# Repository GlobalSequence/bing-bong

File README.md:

## Intro

Bing Bong is a digital drum synthesizer module for Eurorack synthesizers which generates percussive sounds using two different synthesis methods:

- Phase modulation synthesis
- Physical modeling synthesis

This module is intended to offer a versatile array of sounds ranging anywhere from organic substrates to purely synthesized tones. With a wide frequency range, it can fill many roles in an electronic drum kit. Both atonal and tonal sounds can be produced, ranging anywhere from quick transient bursts to long sustained sounds. 

## Block Diagram

## Features
- Versatile drum voice for modular synthesizers
- Switchable phase modulation and physical modeling sound engines
- Mechanical key switch for tactile manual triggering
- CV inputs for all parameters
- 12 bit, 48khz sound

## Synthesis Engines 
### Phase Modulation
#### Overview
The Phase modulation engine is made up of three sine wave operators, fed into one another in series, The first modulator has operator feedback.

The modulation index of each modulator is controlled by the envelope, with each index being set to maximum when the module is triggered, before fading to an index of 0 when the envelope has faded away, effectively creating a sharp sound which softens over time. 

This engine can be used to achieve deep raunchy kick drums, clean ringing chimes, metallic clangs, chirps, and more.
#### Parameters
##### Carrier 
This may be somewhat misleading as this parameter controls the base pitch of the entire voice. 
##### Modulator
Move the pitch of the two modulator oscillators relative to the pitch of the carrier oscillator. The first modulator is always an octave higher than the second modulator. 

When set very high, the carrier frequency (if also set very high) may push the modulator frequencies into interesting territories, or even to oblivion. There is no anti-aliasing in this module, and that's a feature, not a bug! 
##### Pitch Mod
Set the depth by which the envelope affects the pitch of all oscillators. With this parameter set to zero, there is no pitch modulation. As the pitch mod is turned up, the drum hit will start at increasingly higher frequencies and fall to the lowest frequency at the end of the envelope's decay.
##### Decay
Sets the decay time of the envelope. The envelope modulates these other parameters in the engine:
- Modulation index
- Pitch modulation amount
- Internal VCA
By shortening or lengthening the decay time, you can dramatically alter the trajectory of the sound, because all of the parameters dependent on it.

The decay time can be set from a few milliseconds to several seconds, turning the drum module into a sort of faux-drone that can be used for effects and sound scapes, should you wish to venture into that territory.

### Physical Modeling
#### Overview
The physical modeling engine is comprised of a white noise source which is fed into seven parallel band pass filters with a variable Q. 

This engine can be used to achieve organic drum tones ranging from membrane drums of many shapes and sizes, to percussive surfaces made of other materials like glass, metal, wood, and more. 
#### Parameters
##### Cutoff
This sets the cutoff frequency of the central and peripheral band pass filters. 
##### Spread
Pushes the 6 peripheral band pass filters away from the central filter. 3 peripheral filters are set to a lower frequency than the central filter, while the other 3 are higher. The second and third peripheral filters are twice and thrice as far from the central filter as the first on both the higher and lower end, meaning that the filters are always evenly spaced on the frequency spectrum.

When this parameter is set to zero, all of the filters are at the same frequency. 
##### Q
Sets the emphasis of all band pass filters using feedback. As the Q is turned, up, the center frequency of each filter is amplified to the point of self oscillation, making the atonal noise into distinct tones. 

Unlike the traditional VCF > VCA configuration of most modern synthesizers, the filters are set **after** the noise VCA, meaning that you can trigger a sound with a short decay, and if the Q is high enough, the sound will last longer than the decay.

WARNING: Setting the Q to a very high value will create a very loud self oscillation. Since the Q is independent of the decay, the only way to stop the self oscillation is to turn the Q down.
##### Decay
In the physical modeling engine, the envelope only affects the VCA of the voice, attenuating the sound of the filtered noise generator. As mentioned in the Q section, if the Q is set high enough, self oscillation will continue beyond the envelope decay. 

The decay time can be set from a few milliseconds to several seconds, turning the drum module into a sort of faux-drone that can be used for effects and sound scapes, should you wish to venture into that territory.

## DIY
### DISCLAIMER
This project is provided for informational and educational purposes only. By using the provided instructions, code, and hardware designs, you acknowledge that you are solely responsible for your own safety and the cost of any materials or components used.

If you find an error in the project that needs correction, please alert me and I will make it as soon as possible. 
### Build Guide
TODO: add more in depth instructions
#### Software flashing
The software can be uploaded directly to the MCU from the Arduino IDE. To add the Xiao RA4M1 board manager to your Arduino IDE installation, open Arduino Preferences, and add this to the "Additional boards manager URLs" section: https://files.seeedstudio.com/arduino/package_renesas_1.2.0_index.json
#### PCB Ordering
The hardware/gerbers folder contains three separate zip files, for each pcb of the build. Most PCB fabricators take a drag-and-drop upload method for zip files. Each file will likely have to be a separate purchase. 
#### Mounting the MCU board
The Xiao RA4M1 has castellated holes, allowing for the board to be mounted directly to the PCB, but I recommend instead using the optional 1x7 female pin headers marked as OPTIONAL in the BOM. 

This saves you from the headache of having to desolder the whole thing if anything ever goes wrong with the chip, and comes at the cost of the module being a little taller, but it's ultimately up to you. 

## Errata
This section serves as a TODO to me and a 'just so you know' to you.

- The mounting holes are spaced a bit too narrow, so if your Eurorack rails are fixed, you might have to widen the holes with a dremel or drill, or make the edits manually in KiCad. I plan to update the faceplate with oval mounting holes when there's time. 

 - If you have downloaded the PCBs for Bing Bong before 2025.03.25, there is an error where the Seeeduino Xiao board has SMT pads instead of THT pads. This causes the CV input to not connect to the analog pins on the Xiao board. If you have ordered a Bing Bong with the SMT pads instead of the THT pads, you can solder jumper wires to the following pins to the following components on the board which will connect the CV. 
     - Pin 2 - D2 or R10
     - Pin 3 - D3 or R18
     - Pin 4 - D4 or R24
     - Pin 6 - D5 or R30

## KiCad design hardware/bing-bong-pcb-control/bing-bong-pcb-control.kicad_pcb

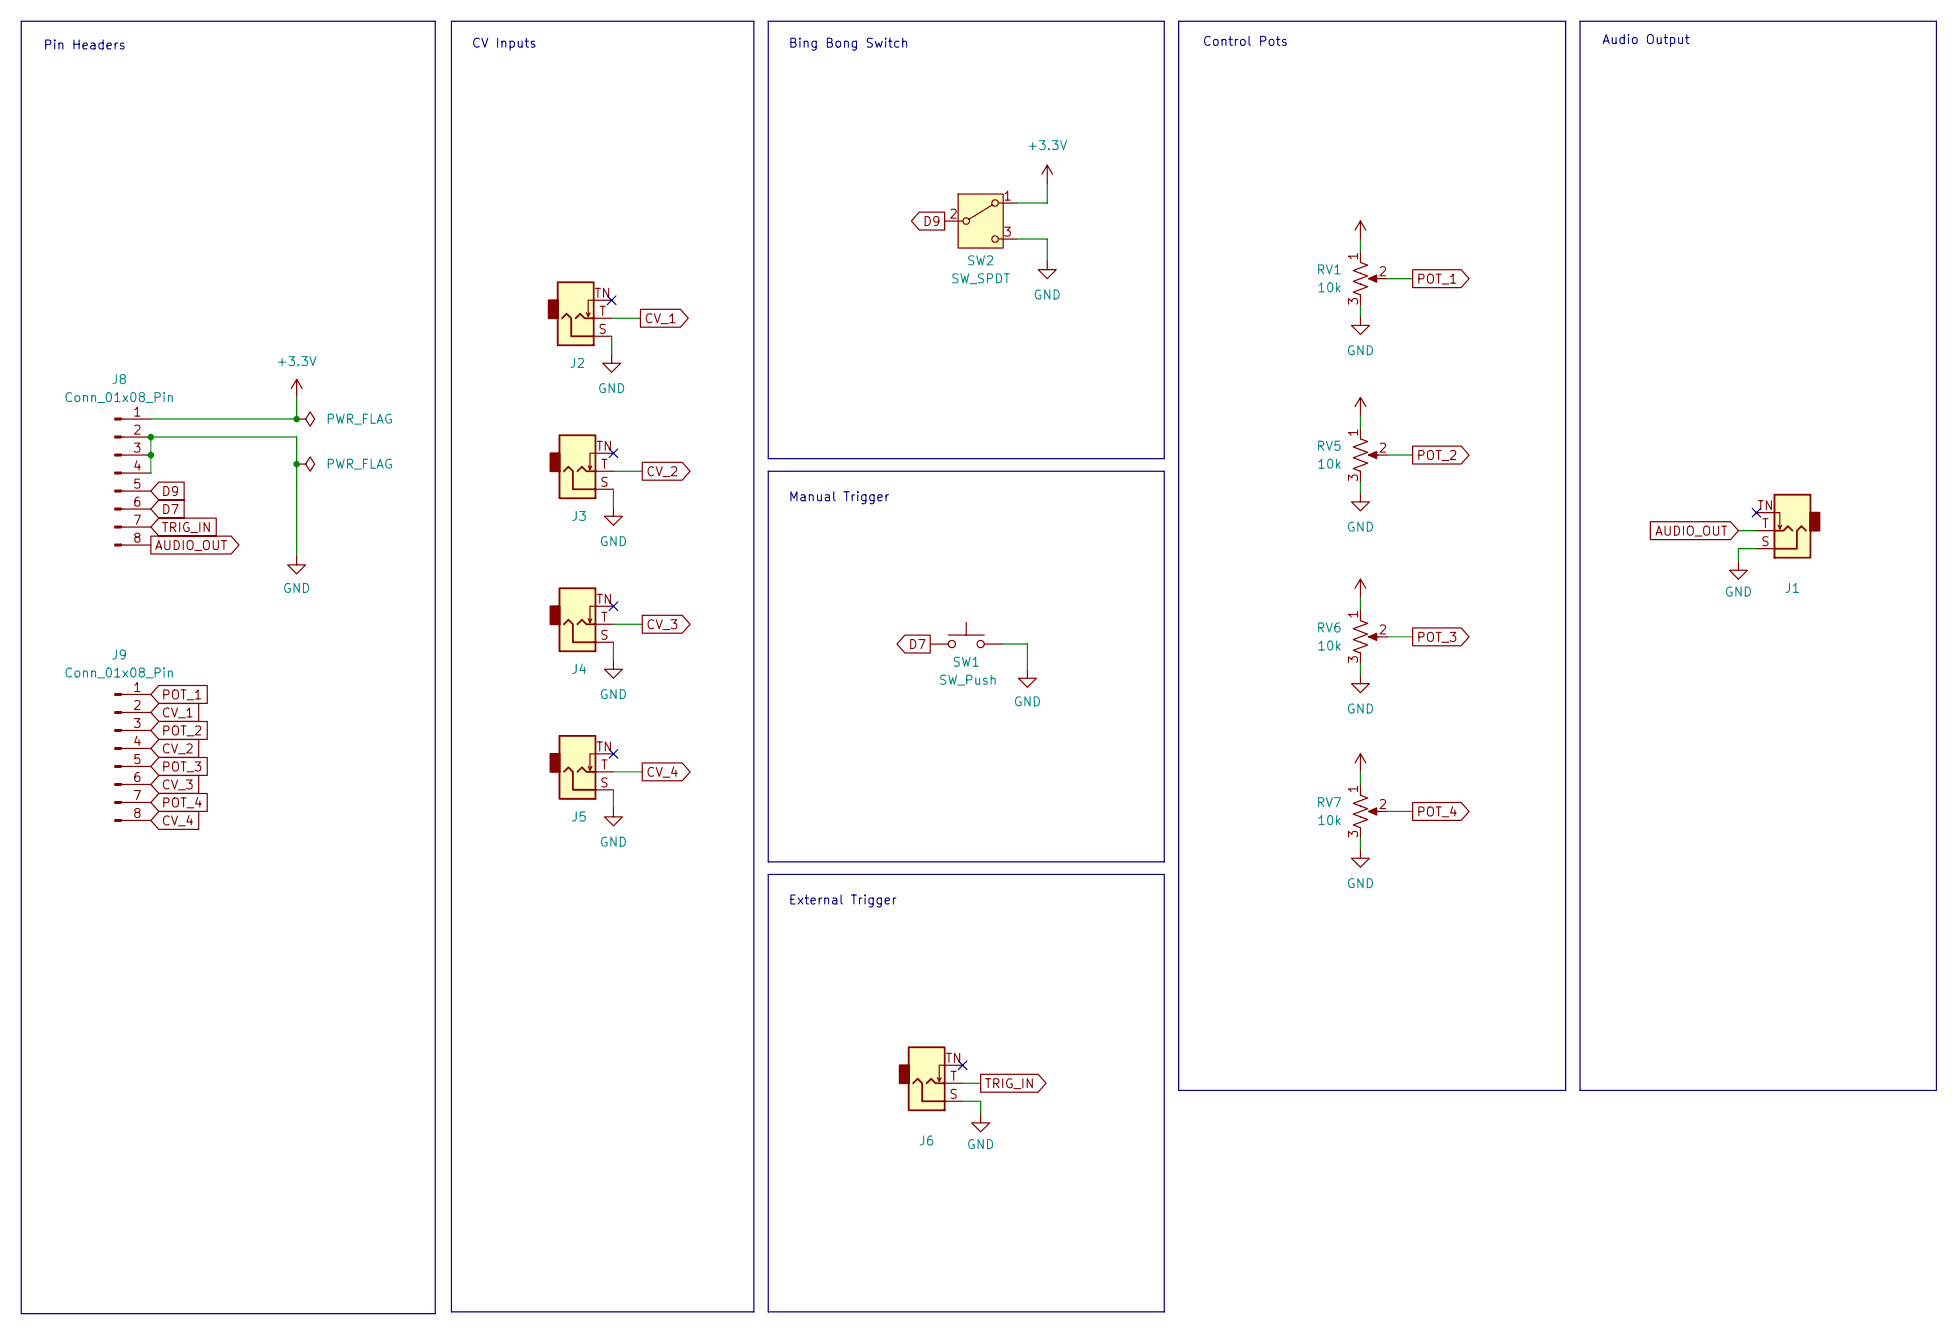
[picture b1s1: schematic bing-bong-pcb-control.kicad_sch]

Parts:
J1, J2, J3, J4, J5, J6: Jack_3.5mm_QingPu_WQP-PJ398SM_Vertical_CircularHoles
J8, J9: Conn_01x08_Pin; PinSocket_1x08_P2.54mm_Vertical
RV1, RV5, RV6, RV7: 10k; Potentiometer_Bourns_PTV09A-1_Single_Vertical
SW1: SW_Push; SW_Cherry_MX_1.00u_PCB
SW2: SW_SPDT; SW_Toggle_Blue_wSlots

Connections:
+3.3V: J8.1, RV1.1, RV5.1, RV6.1, RV7.1, SW2.1 (A)
AUDIO_OUT: J1.T, J8.8
CV_1: J2.T, J9.2
CV_2: J3.T, J9.4
CV_3: J4.T, J9.6
CV_4: J5.T, J9.8
D7: J8.6, SW1.1
D9: J8.5, SW2.2 (B)
GND: J1.S, J2.S, J3.S, J4.S, J5.S, J6.S, J8.2, J8.3, J8.4, RV1.3, RV5.3, RV6.3, RV7.3, SW1.2, SW2.3 (C)
POT_1: J9.1, RV1.2
POT_2: J9.3, RV5.2
POT_3: J9.5, RV6.2
POT_4: J9.7, RV7.2
TRIG_IN: J6.T, J8.7

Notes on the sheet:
Audio Output
Pin Headers
CV Inputs
Manual Trigger
External Trigger
Control Pots
Bing Bong Switch

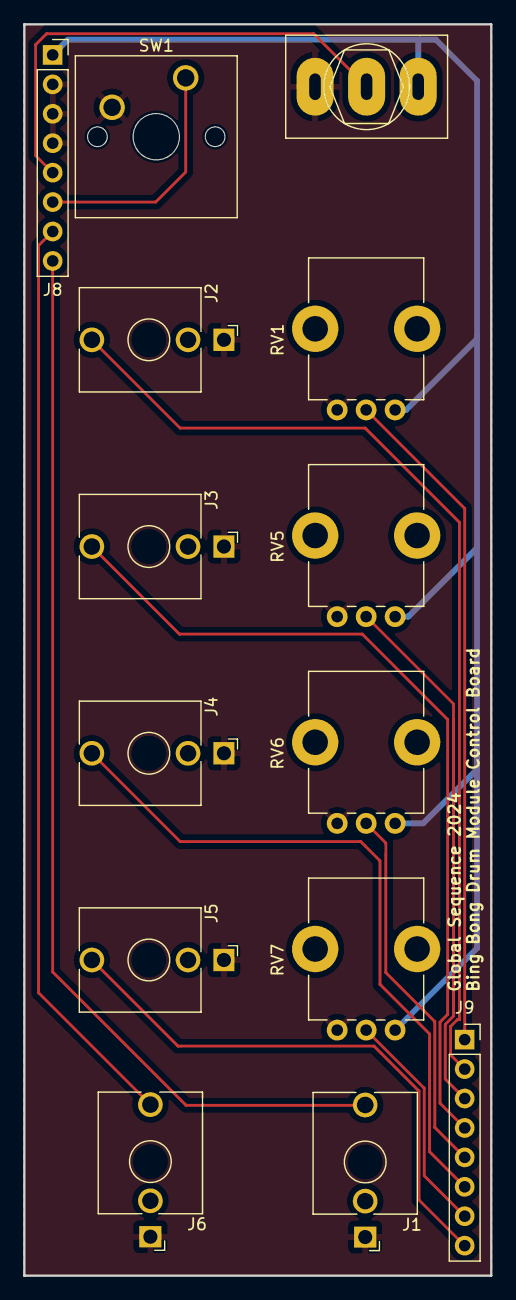
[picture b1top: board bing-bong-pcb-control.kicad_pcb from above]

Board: 2 copper layers, 40.3 x 108.0 mm, 14 parts (0 on the bottom side), 14 nets.

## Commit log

2025-01-09 created repository
2025-01-11 removed old comments
2025-01-11 added board manager notes in software directory
2025-01-12 added bom
2025-01-12 fixed bom
2025-01-12 added missing references to pcb
2025-01-12 changed cv resistor values
2025-02-02 added README, updated BOM
2025-02-02 edited README
2025-02-02 added block diagram
2025-02-02 added images to README
2025-02-03 uploaded images
2025-02-03 modified readme
2025-02-03 added photo
2025-02-03 renamed photo file
2025-02-03 edited photo file
2025-02-03 edited photo
2025-02-03 added photo to readme
2025-02-03 updated bom
2025-02-03 updated schematic
2025-02-17 updated schematic pdf file
2025-02-17 edited note in schematic file
2025-02-17 schematic updated to reflect pcb layout
2025-02-18 fixed missing mask on sw2
2025-03-25 changed smt pads on pcb to tht
2025-03-25 corrected pin names
2025-03-25 updated readme with error warning
2025-03-25 fixed error warning
2025-03-25 fixed error warning again
